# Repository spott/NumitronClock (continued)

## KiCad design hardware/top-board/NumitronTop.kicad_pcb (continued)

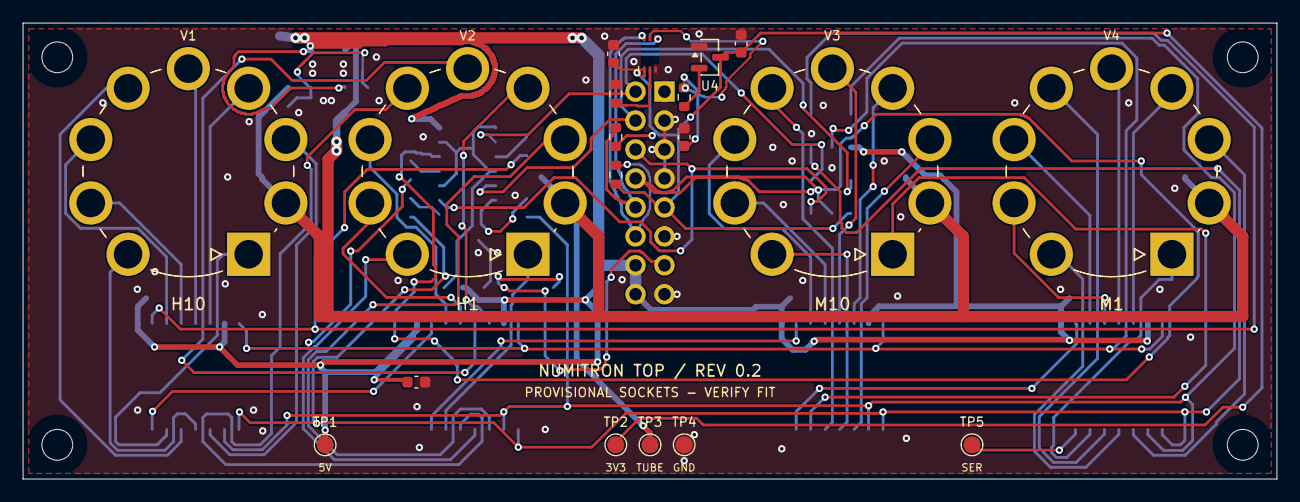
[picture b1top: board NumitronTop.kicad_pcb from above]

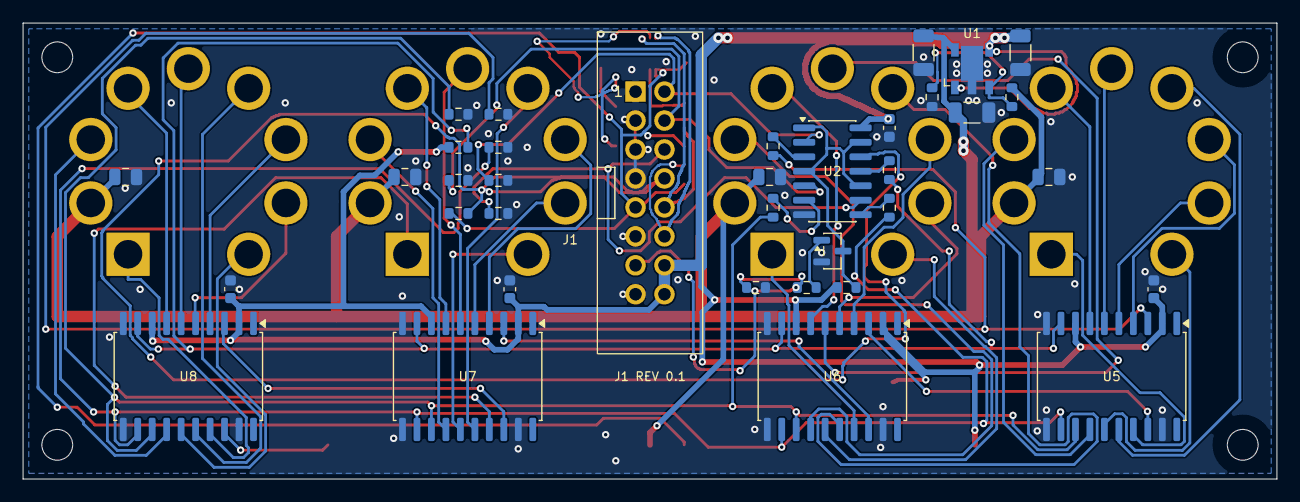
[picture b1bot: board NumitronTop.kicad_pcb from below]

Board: 2 copper layers, 110.0 x 40.0 mm, 59 parts (36 on the bottom side), 61 nets.

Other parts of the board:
H1, H2, H3, H4: M2.5 / NPTH 2.7; MountingHole_2.7mm_M2.5_BothSides

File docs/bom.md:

# Preliminary top-board BOM

Revision 0.2. Generated from the exported native KiCad netlist by `scripts/update_bom.py`. Quantities are for one top board. This is a review BOM, not an order or an assembly release.

| References | Qty | Value / function | Manufacturer part number | Footprint | Assembly | Datasheet |
|---|---:|---|---|---|---|---|
| C1, C2, C3 | 3 | 10u 25V X7R | KYOCERA AVX X7R family; exact order code pending | Capacitor_SMD:C_1206_3216Metric | Fit | [PDF](../datasheets/avx-x7r.pdf) |
| C4, C5, C6, C7, C8, C10, C12, C14 | 8 | 100n 50V X7R | KYOCERA AVX X7R family; exact order code pending | Capacitor_SMD:C_0603_1608Metric | Fit | [PDF](../datasheets/avx-x7r.pdf) |
| C9, C11, C13, C15 | 4 | 1u 25V X7R | KYOCERA AVX X7R family; exact order code pending | Capacitor_SMD:C_0805_2012Metric | Fit | [PDF](../datasheets/avx-x7r.pdf) |
| J1 | 1 | 61201621621 | 61201621621 | Numitron:Wurth_61201621621_2x08_P2.54mm | Fit | [PDF](../datasheets/idc-header.pdf) |
| Q1 | 1 | MMBT3904-7-F | MMBT3904-7-F | Package_TO_SOT_SMD:SOT-23 | Fit | [PDF](../datasheets/mmbt3904.pdf) |
| R1 | 1 | 46.4k 1% | RC0603FR-0746K4L | Resistor_SMD:R_0603_1608Metric | Fit | [PDF](../datasheets/RC0603FR-0746K4L.pdf) |
| R2 | 1 | 10k 1% | RC0603FR-0710KL | Resistor_SMD:R_0603_1608Metric | Fit | [PDF](../datasheets/RC0603FR-0710KL.pdf) |
| R3, R4, R5, R6 | 4 | 33R | RC0603FR-0733RL | Resistor_SMD:R_0603_1608Metric | Fit | [PDF](../datasheets/RC0603FR-0733RL.pdf) |
| R7, R8, R9 | 3 | 100k | RC0603FR-07100KL | Resistor_SMD:R_0603_1608Metric | Fit | [PDF](../datasheets/RC0603FR-07100KL.pdf) |
| R10, R16 | 2 | 2.2k | RC0603FR-072K2L | Resistor_SMD:R_0603_1608Metric | Fit | [PDF](../datasheets/RC0603FR-072K2L.pdf) |
| R11, R12, R13, R14, R17 | 5 | 4.7k | RC0603FR-074K7L | Resistor_SMD:R_0603_1608Metric | Fit | [PDF](../datasheets/RC0603FR-074K7L.pdf) |
| R15, R18 | 2 | 1k | RC0603FR-071KL | Resistor_SMD:R_0603_1608Metric | Fit | [PDF](../datasheets/RC0603FR-071KL.pdf) |
| R19 | 1 | 10k | RC0603FR-0710KL | Resistor_SMD:R_0603_1608Metric | Fit | [PDF](../datasheets/RC0603FR-0710KL.pdf) |
| R20, R21 | 2 | 4.7k | RC0603FR-074K7L | Resistor_SMD:R_0603_1608Metric | DNP | [PDF](../datasheets/RC0603FR-074K7L.pdf) |
| U1 | 1 | AP7361C-Y5-13 | AP7361C-Y5-13 | Numitron:Diodes_SOT89-5_AP7361C | Fit | [PDF](../datasheets/AP7361C.pdf) |
| U2 | 1 | SN74AHCT125DR | SN74AHCT125DR | Package_SO:SOIC-14_3.9x8.7mm_P1.27mm | Fit | [PDF](../datasheets/sn74ahct125.pdf) |
| U3 | 1 | BH1750FVI-TR | BH1750FVI-TR | Numitron:ROHM_WSOF6I_BH1750_NoCenterPad | Fit | [PDF](../datasheets/bh1750fvi.pdf) |
| U4 | 1 | TLV809EA29DBZR | TLV809EA29DBZR | Package_TO_SOT_SMD:SOT-23 | Fit | [PDF](../datasheets/tlv809e.pdf) |
| U5, U6, U7, U8 | 4 | TPIC6B595DWR | TPIC6B595DWR | Package_SO:SOIC-20W_7.5x12.8mm_P1.27mm | Fit | [PDF](../datasheets/tpic6b595.pdf) |
| V1, V2, V3, V4 | 4 | DR2000 / GZC9-A | DR2000 | Numitron:GZC9-A_B9A_Provisional | Tubes in hand; sockets separate below | [PDF](../datasheets/dr2000.pdf) |

## Mechanical and cable items

| Item | Quantity | Selection / status |
|---|---:|---|
| Tube sockets | 4 | Ordered GZC9-A, [Amazon B0BGBJ7L41](https://www.amazon.com/dp/B0BGBJ7L41). [Drawing](../datasheets/GZC9-A_socket-dimensions.jpg) archived; [provisional footprint assumptions](socket.md) authorized 2026-09-25. Assigned to V1-V4 for layout; check physical fit before ordering. |
| Cable female connectors | 2 | Wurth 61201623021, [datasheet](../datasheets/idc-socket.pdf). One at each cable end. |
| Strain-relief caps | 2 | Included in the selected Wurth socket's with-strain-relief specification; confirm supplied pieces and assembled clearance. |
| Ribbon cable | ~150 mm initially | 3M 3365/16, 28 AWG, 1.27 mm pitch, [datasheet](../datasheets/3m-3365-ribbon.pdf). Final length follows the debugging/enclosure clearance check. |
| Board spacers / screws | TBD | Four M2.5 positions with 2.7 mm nonplated holes at (3,3), (107,3), (3,37), (107,37) mm. Target 25-30 mm board separation; confirm actual screw/spacer and cable clearance. |

TP1-TP5 are bare PCB test pads; they require no purchased components. The bottom-board mate of J1 is outside this top-board BOM.

## Assembly notes

- R20/R21 are omitted when the bottom board supplies the I2C pull-ups. All selected resistors are Yageo RC0603, 1%, 0.1 W; individual part specifications are archived.
- Capacitor footprint sizes, voltage ratings and dielectric are specified, but exact order codes remain pending. Select from the archived KYOCERA AVX X7R family, and verify effective capacitance at bias before freezing the BOM. C2+C3 must retain at least 2.2 uF total.
- V1-V4 use Numitron:GZC9-A_B9A_Provisional: assumed 0.5 mm terminal thickness, 18 mm pad circle, 2.5 mm plated holes and 3.8 mm copper pads. The owner authorized using these estimates for layout; verify fit before ordering.
- U3 uses the custom six-land WSOF6I footprint with no soldered centre pad and a front copper keepout; see layout notes for the older package drawing correspondence. U1 and J1 use manufacturer-specific local footprints.
- U1's C507885 identifier comes from the Obsidian plan. Stock, price, assembly-house availability and substitutions have not been qualified.
- Use normal-pinout TLV809EA29DBZR, not an R/V pinout variant. Use AHCT logic, not HC. The four TPIC parts use the wide SOIC-20 package.

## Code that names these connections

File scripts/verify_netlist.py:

#!/usr/bin/env python3
"""Audit KiCad's exported connectivity against the component pin tables.

Does not import the schematic generator: these assertions operate on KiCad's
interpretation of the actual saved schematic, including its hierarchy.
"""
from pathlib import Path
import xml.etree.ElementTree as ET

ROOT = Path(__file__).resolve().parents[1]
tree = ET.parse(ROOT / "review/NumitronTop.net.xml").getroot()
components = {c.attrib["ref"]: c for c in tree.find("components")}
nets = {}
members = {}
checks = 0
for net in tree.find("nets"):
    name = net.attrib["name"]
    members[name] = {(p.attrib["ref"], p.attrib["pin"]) for p in net.findall("node")}
    for node in members[name]:
        assert node not in nets, f"Pin in two nets: {node}"
        nets[node] = name

def require(ref, pin, expected):
    global checks
    actual=nets.get((ref,str(pin)))
    assert actual == expected, f"{ref}.{pin}: {actual!r}, expected {expected!r}"
    checks+=1

def joined(*pins):
    global checks
    names={nets.get((ref,str(pin))) for ref,pin in pins}
    assert len(names)==1 and None not in names, f"Not joined: {pins}: {names}"
    checks+=1

def value(ref, expected):
    global checks
    actual=components[ref].findtext("value")
    assert actual == expected, f"{ref}: {actual!r}, expected {expected!r}"
    checks+=1

assert len(components)==55, f"Unexpected component count: {len(components)}"
assert len({nets[("TP1","1")],nets[("TP2","1")],nets[("TP3","1")],nets[("TP4","1")]})==4, "Power rails shorted"
for pin,name in {1:"GND",2:"SER_3V3",3:"GND",4:"SRCK_3V3",5:"GND",6:"RCK_3V3",7:"GND",8:"BLANK_3V3",9:"+3V3",10:"SDA",11:"GND",12:"SCL",13:"DISPLAY_ARM",14:"+5V",15:"GND",16:"+5V"}.items(): require("J1",pin,name)
for pin,name in {1:"+5V",2:"GND",4:"+5V",5:"V_TUBE"}.items(): require("U1",pin,name)
joined(("U1",3),("R1",2),("R2",1))
require("R1",1,"V_TUBE"); require("R2",2,"GND")
for pin,name in {2:"SER_3V3",5:"SRCK_3V3",9:"RCK_3V3",12:"BLANK_3V3",14:"+5V",7:"GND"}.items(): require("U2",pin,name)
joined(("U2",1),("U2",4),("U2",10),("U2",13),("Q1",3),("R15",2))
require("R15",1,"+5V"); require("Q1",2,"GND")
joined(("Q1",1),("R16",2))
require("R16",1,"DISPLAY_ARM"); require("R17",1,"DISPLAY_ARM"); require("R17",2,"GND")
for output,r,signal in [(3,"R3","SER_5V"),(6,"R4","SRCK_5V"),(8,"R5","RCK_5V"),(11,"R6","BLANK_5V")]:
    joined(("U2",output),(r,1)); require(r,2,signal)
require("R10",1,"+5V"); require("R10",2,"BLANK_5V")
require("R14",1,"+3V3"); require("R14",2,"BLANK_3V3")
for ref,signal in [("R7","SER_5V"),("R8","SRCK_5V"),("R9","RCK_5V")]:
    require(ref,1,signal); require(ref,2,"GND"); value(ref,"100k")
for ref,signal in [("R11","SER_3V3"),("R12","SRCK_3V3"),("R13","RCK_3V3")]:
    require(ref,1,signal); require(ref,2,"GND"); value(ref,"4.7k")
# Preserve the A2 E9 workaround and the sensor address leakage margin.
value("R17","4.7k"); value("R19","10k")
value("R15","1k"); value("R16","2.2k")
for ref in ["U5","U6","U7","U8"]:
    for pin,name in {2:"+5V",8:"+5V",9:"BLANK_5V",10:"GND",11:"GND",19:"GND",12:"RCK_5V",13:"SRCK_5V"}.items(): require(ref,pin,name)
    for pin in [1,20]:
        assert len(members[nets[(ref,str(pin))]])==1, f"NC pin wired: {ref}.{pin}"
require("U5",3,"SER_5V")
joined(("U5",18),("U6",3)); joined(("U6",18),("U7",3)); joined(("U7",18),("U8",3)); joined(("U8",18),("TP5",1))
# Physical RCA socket pins, independent of graphical segment labels.
for driver,tube in [("U5","V1"),("U6","V2"),("U7","V3"),("U8","V4")]:
    assert components[tube].findtext("footprint")=="Numitron:GZC9-A_B9A_Provisional", f"Missing provisional socket footprint: {tube}"
    checks+=1
    require(tube,2,"V_TUBE")
    for drain,base in [(4,7),(5,8),(6,5),(7,4),(14,3),(15,9),(16,6),(17,1)]:
        joined((driver,drain),(tube,base))
        assert len(members[nets[(tube,str(base))]])==2, f"Unexpected segment branch at {tube}.{base}"
for pin,name in {1:"+3V3",3:"GND",4:"SDA",6:"SCL"}.items(): require("U3",pin,name)
require("U4",1,"GND"); require("U4",3,"+3V3")
joined(("U4",2),("R18",1)); joined(("U3",5),("R18",2),("C6",1)); joined(("U3",2),("R19",1))
require("R19",2,"GND"); require("C6",2,"GND")
for r,signal in [("R20","SDA"),("R21","SCL")]:
    require(r,1,"+3V3"); require(r,2,signal)
    assert any(p.attrib.get("name")=="dnp" for p in components[r].findall("property")), f"{r} must be DNP"

# Ensure every actual part links to a committed document, not a stale web-only field.
for ref,part in components.items():
    ds=part.findtext("datasheet") or ""
    if ref.startswith("TP"): continue
    path=Path(ds.replace("${KIPRJMOD}",str(ROOT/"hardware/top-board")))
    assert path.is_file(), f"Missing datasheet for {ref}: {ds}"
    assert path.read_bytes().startswith(b"%PDF"), f"Not a PDF: {path}"
    checks+=1

text=f"PASS: {checks} connectivity/document assertions; {len(components)} components; {len(members)} nets.\n"
text+="Includes rail separation, all IDC pins, SRCK pin 13, all TPIC grounds, 32 filament paths, cascade order, blanking, DVI reset and DNP I2C pull-ups.\n"
text+="Not verified on hardware. Provisional socket dimensions and pin-1 decimal connection need checking before ordering; custom package lands and assembly fit require the normal hardware check.\n"
(ROOT/"review/connectivity.txt").write_text(text)
print(text,end="")

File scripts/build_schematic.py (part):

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    s.rail(rp["1"],"+5V"); s.wire(rp["2"],qt["3"])
    s.junction((243.84,71.12))
    # Split the collector wire at the labeled junction for explicit connectivity.
    s.wire((243.84,71.12),(261.62,71.12)); s.label("BUF_OE_N",(261.62,71.12))
    rb=s.add("R","R16",215.9,83.82,"2.2k",angle=90)
    s.wire(rb["2"],qt["1"]); s.stub(rb["1"],"DISPLAY_ARM","left",7.62,True)
    s.passive("R","R17","4.7k",215.9,113.03,"DISPLAY_ARM","GND")
    s.text("ARM = 0 / disconnected: buffers high impedance.\nR10 holds BLANK_5V high; tubes stay off.\nARM = 1: Q1 enables all four buffers.\nKeep BLANK high while arming and loading data.\nNo 5 V pull-up connects directly to an MCU pin.",279.4,55.88)
    s.text("5 V BUS DEFAULTS",17.78,128.27,1.524)
    for i,(x,net) in enumerate([(40.64,"SER_5V"),(81.28,"SRCK_5V"),(121.92,"RCK_5V")],7):
        s.passive("R",f"R{i}","100k",x,147.32,net,"GND")
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    s.rail(sup["3"],"+3V3"); s.rail(sup["1"],"GND","down")
    rd=s.add("R","R18",299.72,172.72,"1k",angle=90)
    s.wire(sup["2"],rd["1"]); s.wire(rd["2"],sensor["5"])
    s.label("ALS_DVI",(312.42,172.72))
    cd=s.add("C","C6",320.04,195.58,"100n 50V X7R")
    s.wire(cd["1"],(320.04,172.72)); s.junction((320.04,172.72)); s.rail(cd["2"],"GND","down")
    s.stub(sensor["2"],"ALS_ADDR","left",5.08)
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    root.wire(u["4"],(165.1,58.42)); root.rail((165.1,58.42),"+5V")
    root.wire(u["1"],(165.1,63.5)); root.wire((165.1,63.5),(165.1,58.42)); root.junction((165.1,58.42))
    root.rail(u["2"],"GND","down")
    root.wire(u["5"],(254,58.42)); root.label("V_TUBE",(254,58.42),True)
    rt=root.add("R","R1",231.14,73.66,"46.4k 1%",fields={"MPN":"RC0603FR-0746K4L","Manufacturer":"Yageo"})
    rb=root.add("R","R2",231.14,96.52,"10k 1%",fields={"MPN":"RC0603FR-0710KL","Manufacturer":"Yageo"})
    root.wire(rt["1"],(231.14,58.42)); root.junction((231.14,58.42))
    root.wire(rt["2"],(231.14,83.82)); root.wire((231.14,83.82),rb["1"])
    root.wire(u["3"],(215.9,63.5)); root.wire((215.9,63.5),(215.9,83.82)); root.wire((215.9,83.82),(231.14,83.82))
    root.junction((231.14,83.82)); root.label("LDO_FB",(215.9,83.82)); root.rail(rb["2"],"GND","down")
    for ref,x,net in [("C1",144.78,"+5V"),("C2",281.94,"V_TUBE"),("C3",325.12,"V_TUBE")]:
        root.passive("C",ref,"10u 25V X7R",x,78.74,net,"GND",fp="Capacitor_SMD:C_1206_3216Metric",fields={"Manufacturer":"KYOCERA AVX","Selection":"X7R family; exact order code / DC bias pending"})
    root.text("0.8 x (1 + 46.4k / 10k) = 4.512 V nominal.\nDo not increase voltage to compensate driver loss.\nC2+C3: verify >= 2.2 uF effective total at bias.\nGND tab needs copper for heat spreading.",266.7,109.22)
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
